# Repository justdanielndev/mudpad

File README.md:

# Müdpad

Müdpad is an (almost) 4×4, 15-key macropad with a single rotary encoder, that I'll probably use for random shenanigans and to control my Mac :D

## Overview

It has one clickable rotary encoder (used to control music or other media) and (of course, lol) buttons, in this case 15, in a 4x4 grid

## Stuff it has

- **15 mechanical switches** arranged in an almost 4×4 grid
- **1 rotary encoder** (with push)
- **No OLED or screen**; sadly couldn't fit those with the Xiao

- ## Bill of Materials (BOM)

| Component | Quantity |
|-----------|----------|
| Cherry MX Switches | 15 |
| Rotary encoder (EC11) | 1 |
| XIAO RP2040 | 1 |
| PCB | 1 |
| Diodes (1N4148) | 15 |
| USB-C Cable | 1 |
| 3D Printed Case | 1 |
| 3D Printed Knob for the encoder | 1 |
| Keycaps | 15 |

## Screenshots

Schematic (extra button just in case and to not break 4x4 structure):

CAD:

PCB (design):

PCB (3D):

### Tools Required

- Soldering iron (temperature controlled recommended)
- Solder (leaded or lead-free)
- Flush cutters
- Multimeter (for testing)
- Firmware flashing tool (depends on microcontroller)

## Layout

It's composed of a 4x4 grid with the exception of the bottom right key being actually a rotary encoder.

## Set up

You basically have to:

1. **Flash the chosen firmware** to your microcontroller (following that firmware's documentation)
2. **Solder the switches**, diodes, and encoder
3. **Configure your keymap**
4. **Use it** :3

(psst, this project was submitted to Moonshot, check it out!)
<div align="center">
  
</div>

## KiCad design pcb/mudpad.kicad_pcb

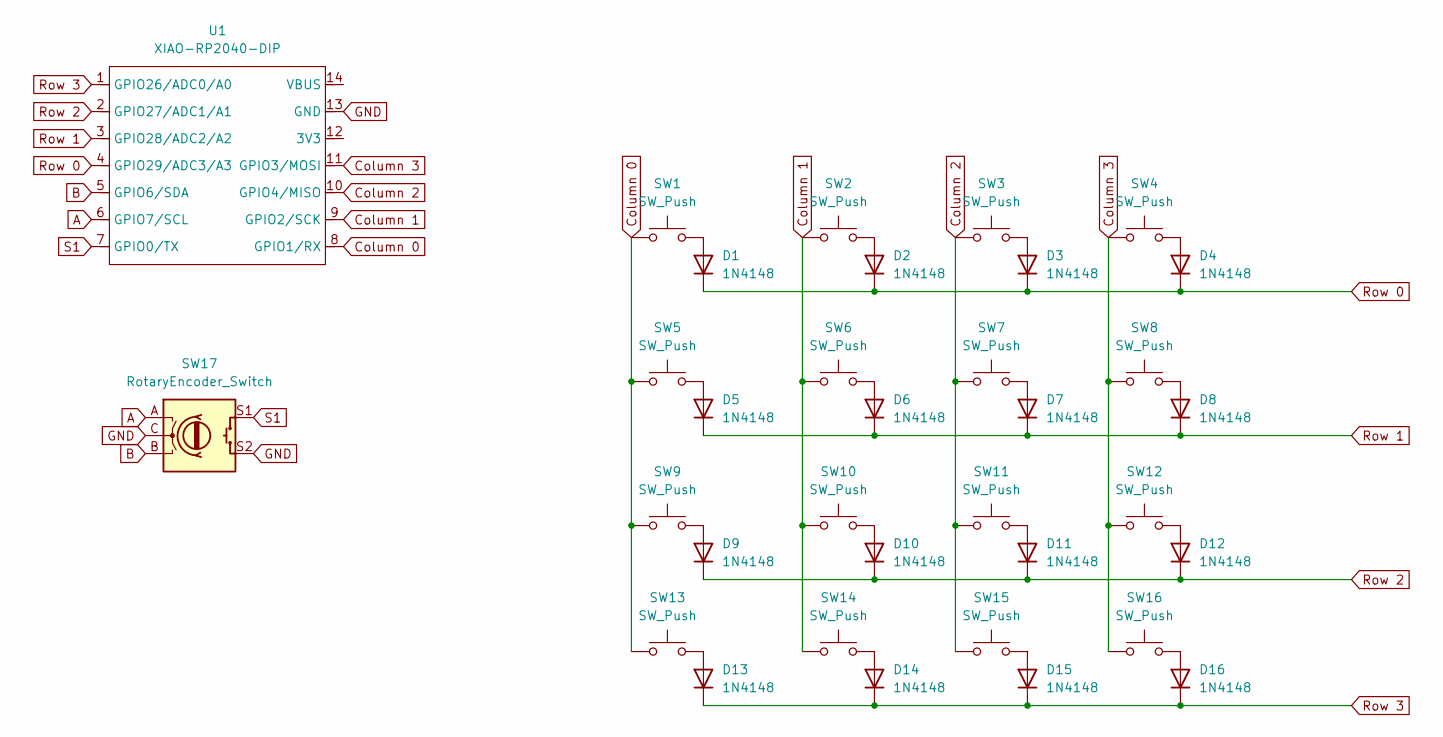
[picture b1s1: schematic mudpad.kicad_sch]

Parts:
D1, D2, D3, D4, D5, D6, D7, D8, D9, D10, D11, D12, D13, D14, D15, D16: 1N4148; D_DO-35_SOD27_P7.62mm_Horizontal
SW1, SW2, SW3, SW4, SW5, SW6, SW7, SW8, SW9, SW10, SW11, SW12, SW13, SW14, SW15, SW16: SW_Push; SW_Cherry_MX_1.00u_PCB
SW17: RotaryEncoder_Switch; RotaryEncoder_Alps_EC11E-Switch_Vertical_H20mm
U1: XIAO-RP2040-DIP

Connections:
A: SW17.A, U1.6 (GPIO7/SCL)
B: SW17.B, U1.5 (GPIO6/SDA)
Column 0: SW1.1, SW5.1, SW9.1, SW13.1, U1.8 (GPIO1/RX)
Column 1: SW2.1, SW6.1, SW10.1, SW14.1, U1.9 (GPIO2/SCK)
Column 2: SW3.1, SW7.1, SW11.1, SW15.1, U1.10 (GPIO4/MISO)
Column 3: SW4.1, SW8.1, SW12.1, SW16.1, U1.11 (GPIO3/MOSI)
GND: SW17.C, SW17.S2, U1.13 (GND)
unnamed: D1.2 (A), SW1.2
unnamed: D2.2 (A), SW2.2
unnamed: D3.2 (A), SW3.2
unnamed: D4.2 (A), SW4.2
unnamed: D5.2 (A), SW5.2
unnamed: D6.2 (A), SW6.2
unnamed: D7.2 (A), SW7.2
unnamed: D8.2 (A), SW8.2
unnamed: D9.2 (A), SW9.2
unnamed: D10.2 (A), SW10.2
unnamed: D11.2 (A), SW11.2
unnamed: D12.2 (A), SW12.2
unnamed: D13.2 (A), SW13.2
unnamed: D14.2 (A), SW14.2
unnamed: D15.2 (A), SW15.2
unnamed: D16.2 (A), SW16.2
Row 0: D1.1 (K), D2.1 (K), D3.1 (K), D4.1 (K), U1.4 (GPIO29/ADC3/A3)
Row 1: D5.1 (K), D6.1 (K), D7.1 (K), D8.1 (K), U1.3 (GPIO28/ADC2/A2)
Row 2: D9.1 (K), D10.1 (K), D11.1 (K), D12.1 (K), U1.2 (GPIO27/ADC1/A1)
Row 3: D13.1 (K), D14.1 (K), D15.1 (K), D16.1 (K), U1.1 (GPIO26/ADC0/A0)
S1: SW17.S1, U1.7 (GPIO0/TX)

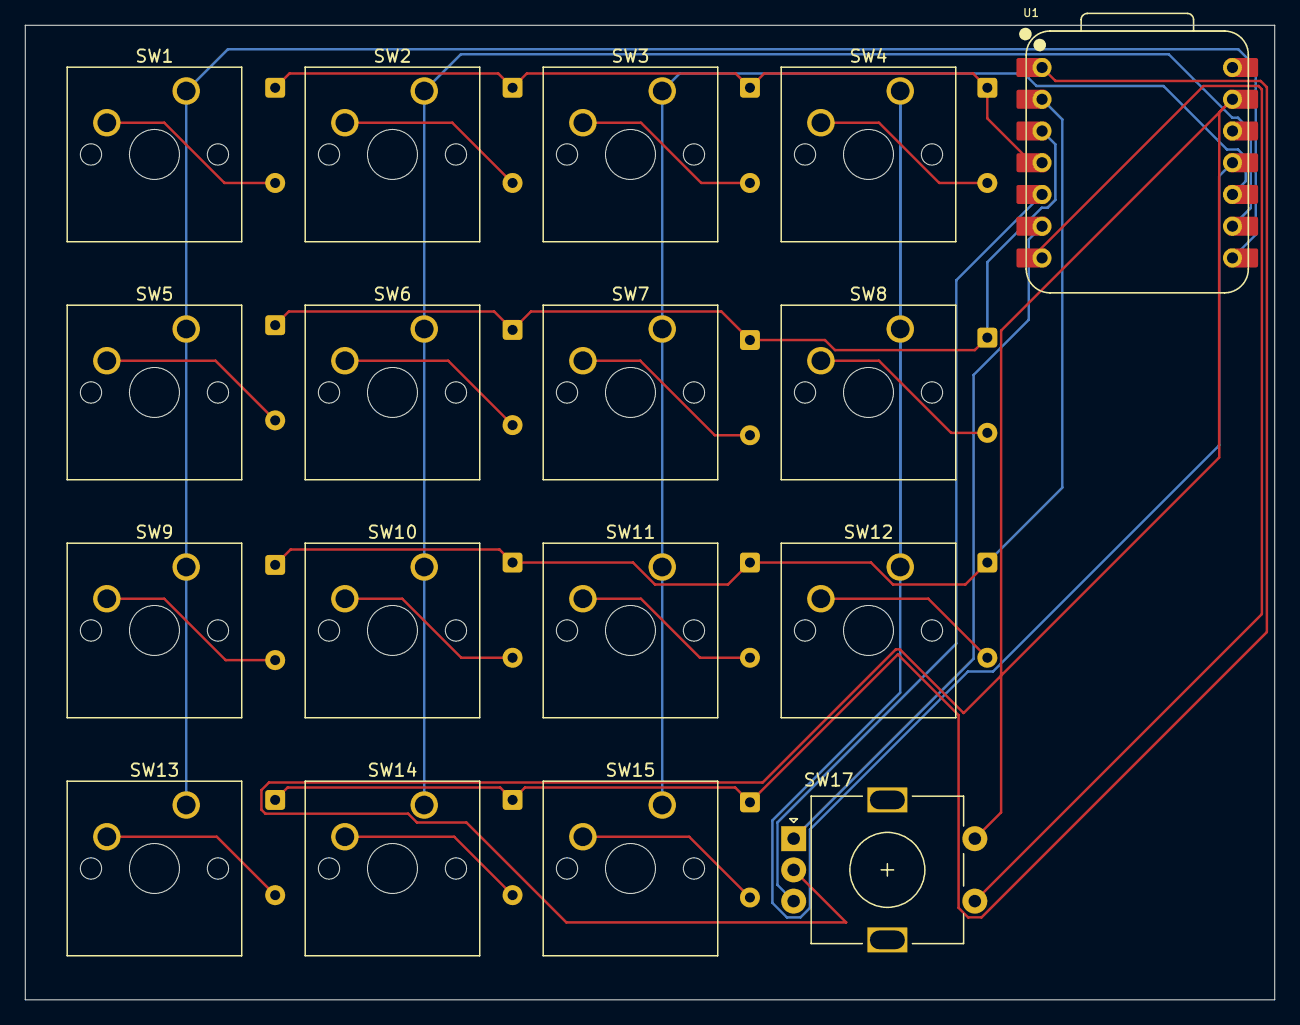
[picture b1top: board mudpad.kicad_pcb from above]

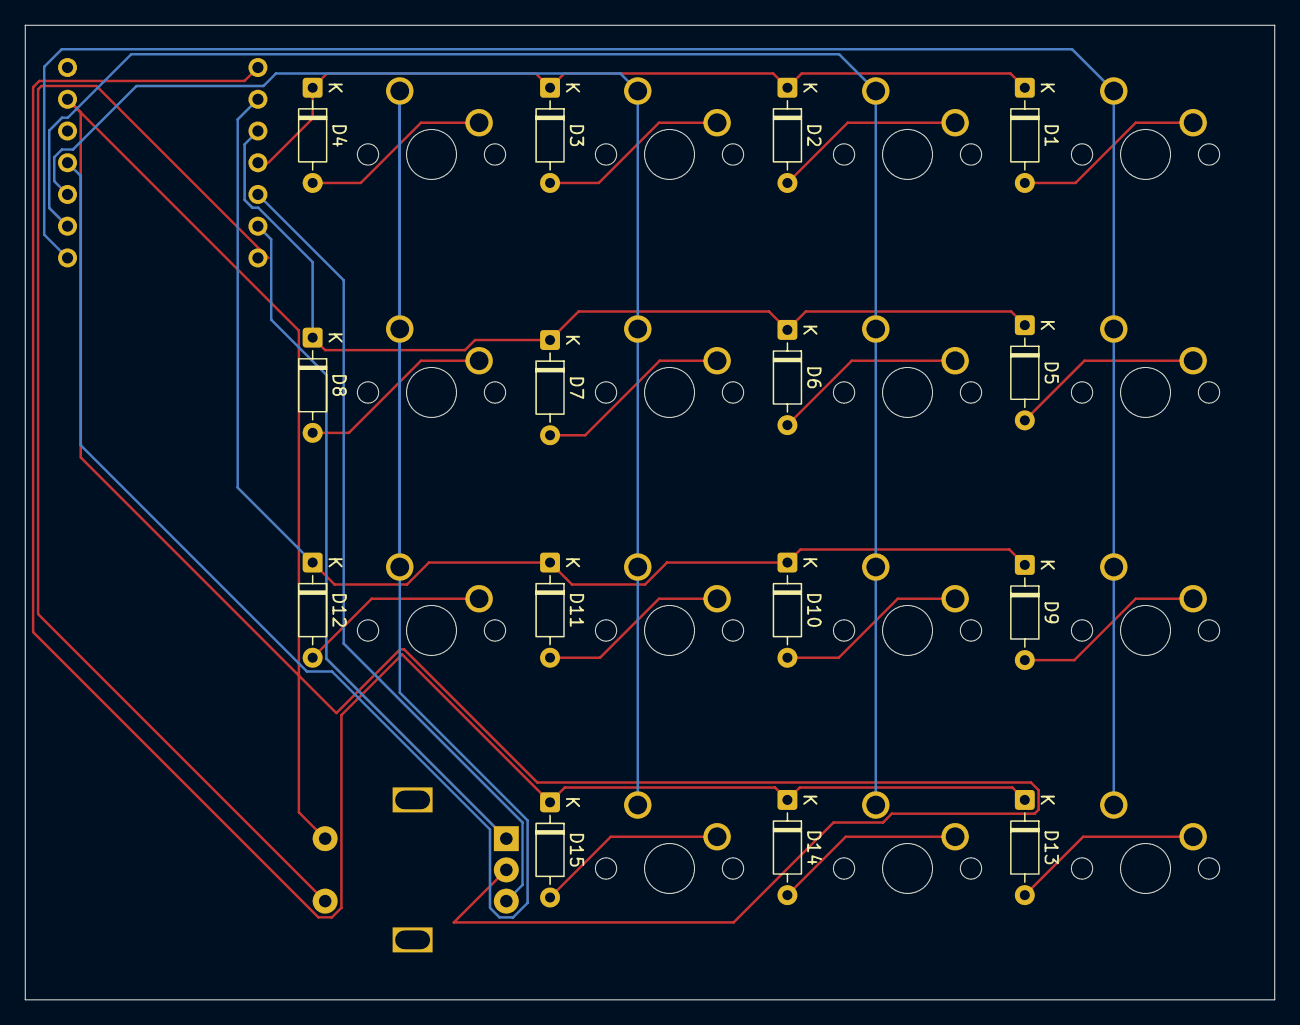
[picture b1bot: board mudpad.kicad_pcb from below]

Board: 2 copper layers, 100.0 x 78.0 mm, 32 parts (15 on the bottom side), 27 nets.

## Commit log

2025-12-02 Created kmk code for the pad
2025-12-02 Uploaded CAD and PCB files
2025-12-02 Added README!
2025-12-02 Add screenshots to README
2025-12-03 Changed wording
2025-12-03 Changed images to Hack Club CDN
2025-12-04 Update README with PCB image
2025-12-10 moonshot banner
